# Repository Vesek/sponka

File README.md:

[English README](/README_en.md)
# sponka
RGB sponka na vlasy, postavená na flex PCB
### ***velice work in progress***
## Komponenty
- CH32V003
	- velice low-cost MCU, dostatečné na ovládání LED
	- chtěl jsem se s ním naučit
- WS2812B-MINI
	- Menší verze WS2812B
- TP4057
	- Nabíječ baterie s ochranou
	- můžete znát z většiny Li-ion nabíjecích desek z Aliexpressu
- DW01A
	- Ochrana samotné baterie
	- Některé baterie mají vestavěné, pro ostatní je zde
## Software
Software je napsaný s vývojovým prostředím [ch32v003fun](https://github.com/cnlohr/ch32v003fun) - open-source a lightweight stack pro programování těchto čipů

### Programování desky
Na desce jsou vyvedeny 3 piny pro SWIO. Výrobce čipu se bohužel rozhodl zavést
nestandardní "spin-off" SWD, takže potřebujete kompatibilní programátor.

Mimo oficiálního programátoru existují i SW programátory na různé MCU, některé lze najít v README [ch32v003fun](https://github.com/cnlohr/ch32v003fun),
existují ale i verze pro [Flipper Zero](https://github.com/sukvojte/wch_swio_flasher)a [RPi Pico](https://github.com/aappleby/picorvd).

Zapojení jednotlivých programátorů můžete najít v jejich README a
pinout SWIO je napsaný na spodní straně desky.

Software zkompilujete a nahrajete pomocí:
```bash
make
```
Nezapoměňte před tím stáhnout submoduly:
```bash
git submodule update --init
```

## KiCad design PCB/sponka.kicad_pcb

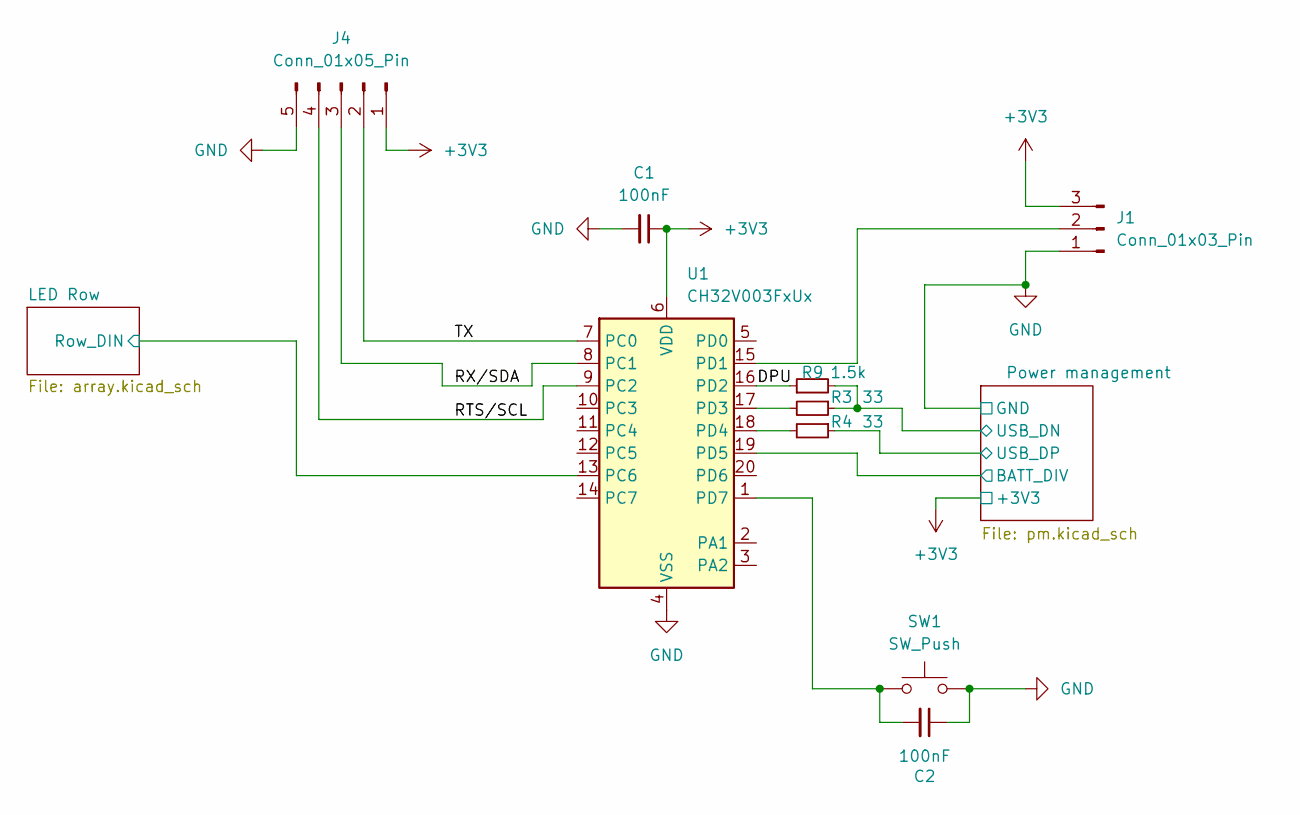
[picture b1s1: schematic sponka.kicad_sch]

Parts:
C1, C2: 100nF; C_0402_1005Metric
J1: Conn_01x03_Pin; pogo_pins_1_3
J4: Conn_01x05_Pin; pogo_pins_1_5
R3, R4: 33; R_0402_1005Metric
R9: 1.5k; R_0402_1005Metric
SW1: SW_Push; SW_SPST_B3U-1000P
U1: CH32V003FxUx; QFN-20-1EP_3x3mm_P0.4mm_EP1.65x1.65mm_ThermalVias

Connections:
+3V3: C1.1, J1.3, J4.1, U1.6 (VDD); also elsewhere on the board
/DPU: R9.1, U1.16 (PD2)
/LED Row/Row_DIN: U1.13 (PC6); also elsewhere on the board
/Power management/BATT_DIV: U1.19 (PD5); also elsewhere on the board
/Power management/USB_DN: R3.1, R9.2; also elsewhere on the board
/Power management/USB_DP: R4.1; also elsewhere on the board
/RTS/SCL: J4.4, U1.9 (PC2)
/RX/SDA: J4.3, U1.8 (PC1)
/TX: J4.2, U1.7 (PC0)
GND: C1.2, C2.1, J1.1, J4.5, SW1.2, U1.4 (VSS), U1.21 (VSS); also elsewhere on the board
unnamed: J1.2, U1.15 (PD1)
unnamed: R3.2, U1.17 (PD3)
unnamed: R4.2, U1.18 (PD4)
unnamed: C2.2, SW1.1, U1.1 (PD7)

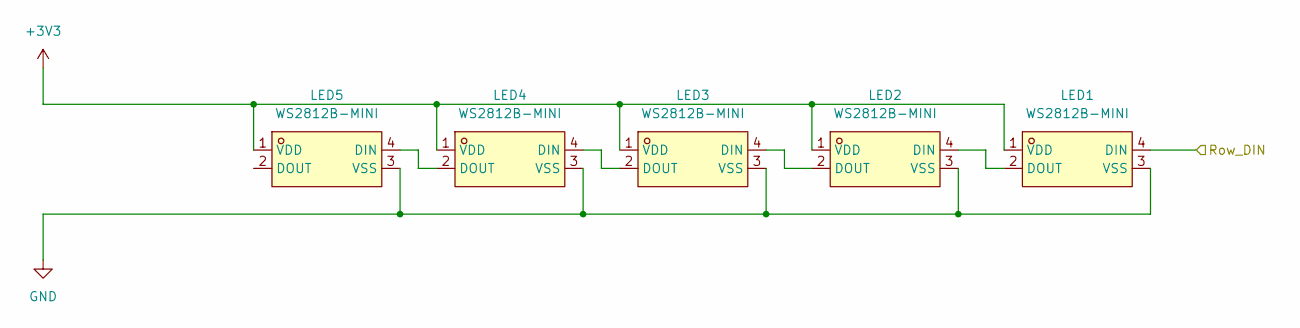
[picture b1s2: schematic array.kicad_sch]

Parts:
LED1, LED2, LED3, LED4, LED5: WS2812B-MINI; LED-SMD_4P-L3.5-W3.5-TL_WS2812B; LCSC Part C527089

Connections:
+3V3: LED1.1 (VDD), LED2.1 (VDD), LED3.1 (VDD), LED4.1 (VDD), LED5.1 (VDD); also elsewhere on the board
/LED Row/Row_DIN: LED1.4 (DIN); also elsewhere on the board
GND: LED1.3 (VSS), LED2.3 (VSS), LED3.3 (VSS), LED4.3 (VSS), LED5.3 (VSS); also elsewhere on the board
unnamed: LED1.2 (DOUT), LED2.4 (DIN)
unnamed: LED2.2 (DOUT), LED3.4 (DIN)
unnamed: LED3.2 (DOUT), LED4.4 (DIN)
unnamed: LED4.2 (DOUT), LED5.4 (DIN)

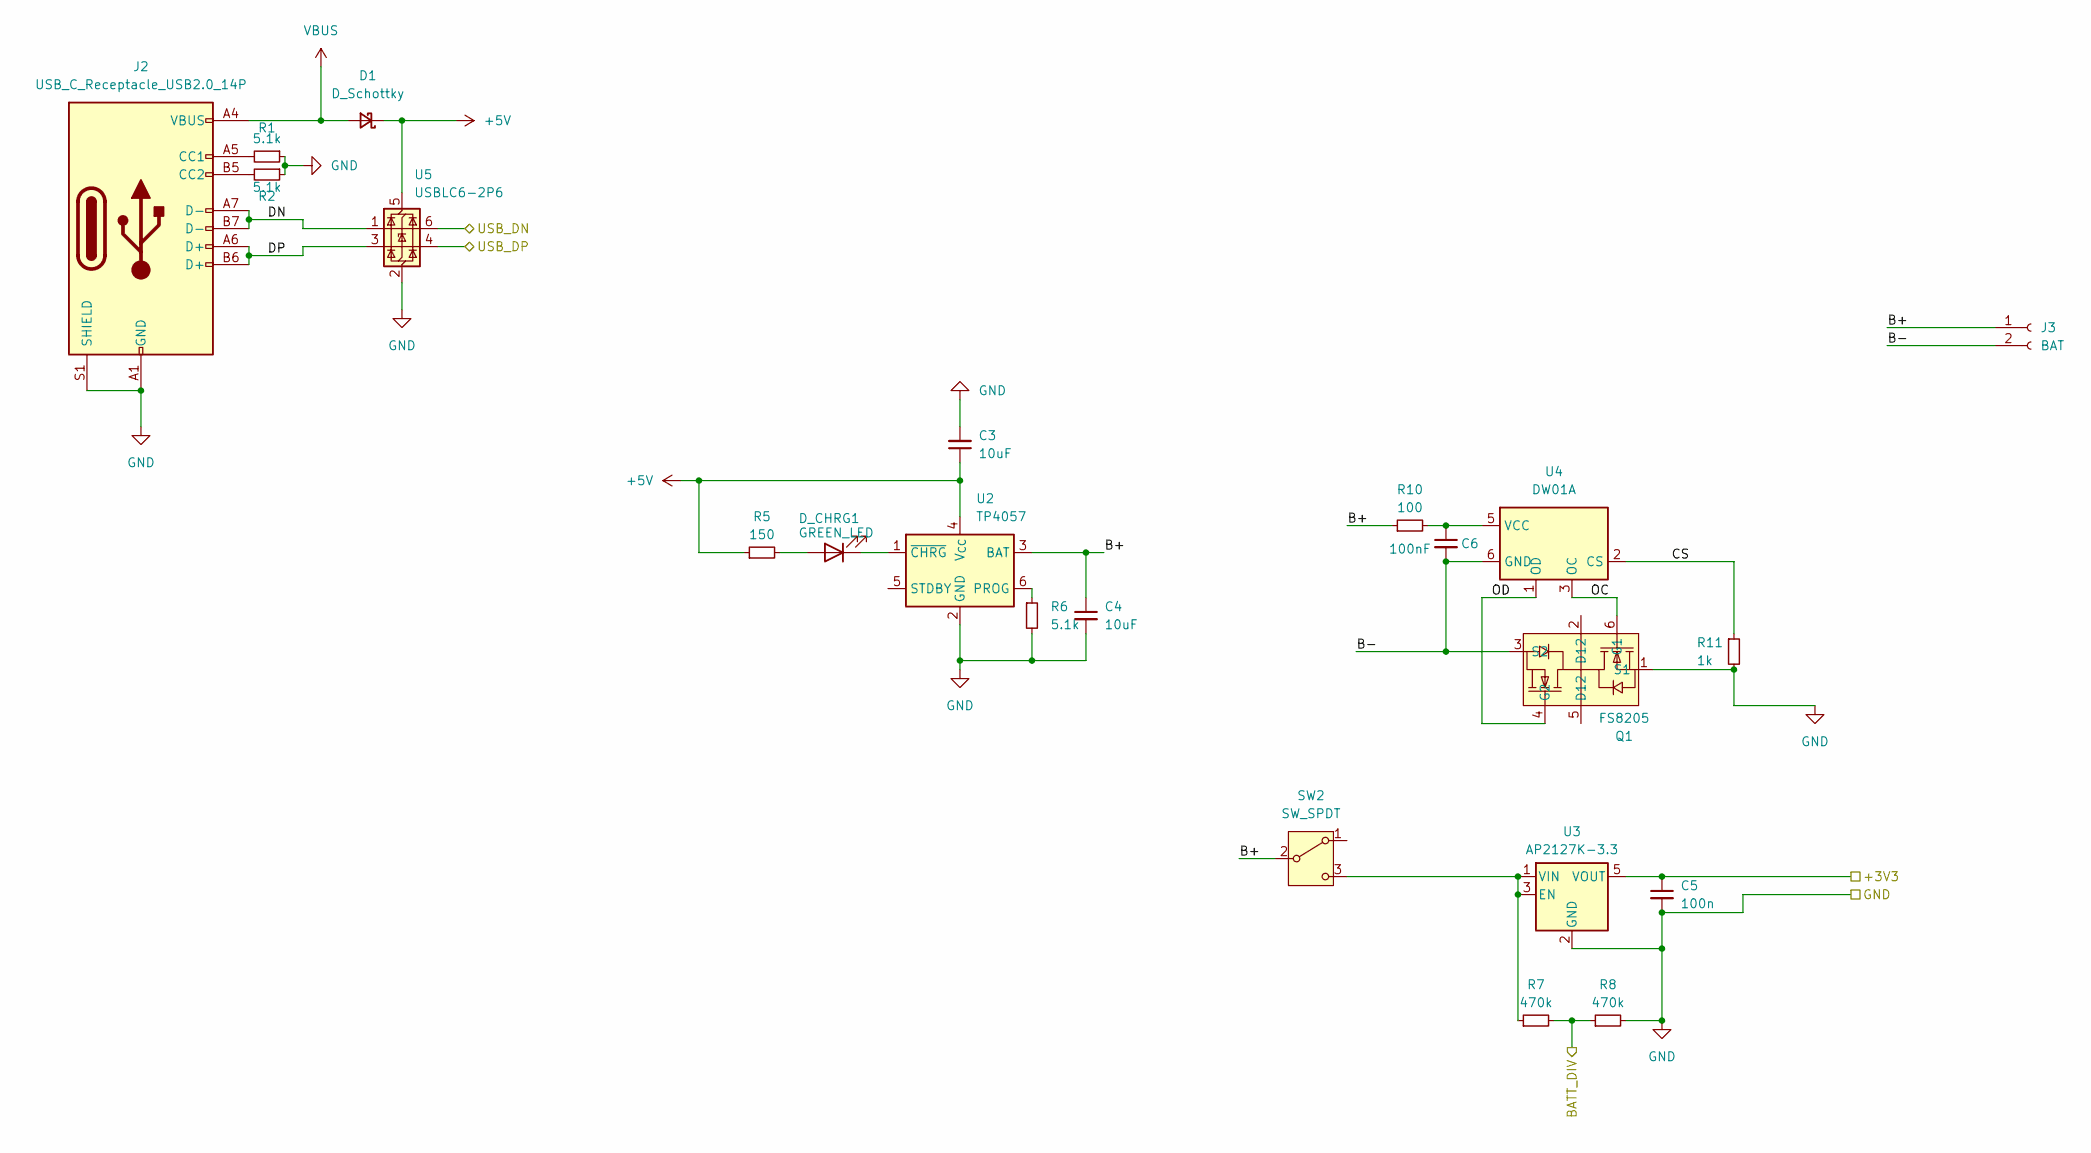
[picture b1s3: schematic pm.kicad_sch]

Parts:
C3, C4: 10uF; C_0402_1005Metric
C5: 100n; C_0402_1005Metric
C6: 100nF; C_0402_1005Metric
D1: D_Schottky; D_0402_1005Metric
D_CHRG1: GREEN_LED; LED_0603_1608Metric
J2: USB_C_Receptacle_USB2.0_14P; USB_C_Receptacle_G-Switch_GT-USB-7010ASV
J3: BAT; JST_SH_SM02B-SRSS-TB_1x02-1MP_P1.00mm_Horizontal
Q1: FS8205; SOT-23-6; LCSC Part C32254
R1, R2, R6: 5.1k; R_0402_1005Metric
R5: 150; R_0402_1005Metric
R7, R8: 470k; R_0402_1005Metric
R10: 100; R_0402_1005Metric
R11: 1k; R_0402_1005Metric
SW2: SW_SPDT; SW_SPDT_PCM12
U2: TP4057; TSOT-23-6
U3: AP2127K-3.3; SOT-23-5
U4: DW01A; SOT-23-6
U5: USBLC6-2P6; SOT-666

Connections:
+3V3: C5.1, U3.5 (VOUT); also elsewhere on the board
+5V: C3.1, D1.1 (K), R5.1, U2.4 (V_{CC}), U5.5 (VBUS)
/Power management/B+: C4.1, J3.1, R10.1, SW2.2 (B), U2.3 (BAT)
/Power management/B-: C6.2, J3.2, Q1.3 (S2), U4.6 (GND)
/Power management/BATT_DIV: R7.2, R8.1; also elsewhere on the board
/Power management/CS: R11.1, U4.2 (CS)
/Power management/DN: J2.A7 (D-), J2.B7 (D-), U5.1 (I/O1)
/Power management/DP: J2.A6 (D+), J2.B6 (D+), U5.3 (I/O2)
/Power management/OC: Q1.6 (G1), U4.3 (OC)
/Power management/OD: Q1.4 (G2), U4.1 (OD)
/Power management/USB_DN: U5.6 (I/O1); also elsewhere on the board
/Power management/USB_DP: U5.4 (I/O2); also elsewhere on the board
GND: C3.2, C4.2, C5.2, J2.A1 (GND), J2.A12 (GND), J2.B1 (GND), J2.B12 (GND), J2.S1 (SHIELD), Q1.1 (S1), R1.1, R2.1, R6.2, R8.2, R11.2, U2.2 (GND), U3.2 (GND), U5.2 (GND); also elsewhere on the board
unnamed: D_CHRG1.2 (A), R5.2
unnamed: D_CHRG1.1 (K), U2.1 (~CHRG)
unnamed: J2.A5 (CC1), R1.2
unnamed: J2.B5 (CC2), R2.2
unnamed: R7.1, SW2.3 (C), U3.1 (VIN), U3.3 (EN)
unnamed: R6.1, U2.6 (PROG)
unnamed: C6.1, R10.2, U4.5 (VCC)
VBUS: D1.2 (A), J2.A4 (VBUS), J2.A9 (VBUS), J2.B4 (VBUS), J2.B9 (VBUS)

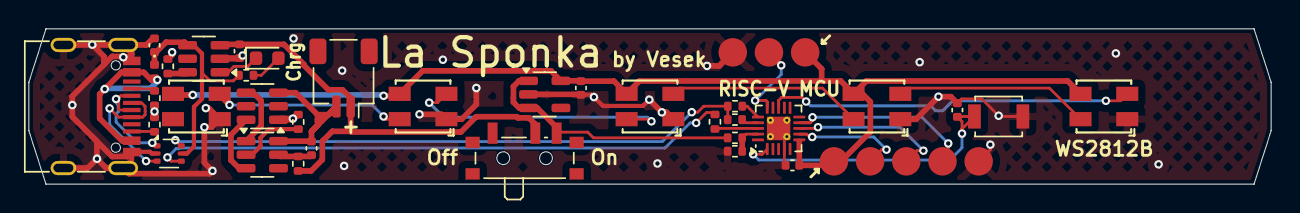
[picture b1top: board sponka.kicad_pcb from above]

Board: 2 copper layers, 87.2 x 10.9 mm, 36 parts (0 on the bottom side), 34 nets.

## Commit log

2024-09-05 Made first PCB
2024-09-06 PCB V2
2024-09-07 New PCB design
2024-09-07 New PCB revision
2024-09-08 Probably the final update
2024-09-08 Small updates to PCB
2024-09-10 Made smol :) Anyway, this is just WIP, still working on it
2024-09-10 Progress update
2024-09-11 Probably done?
2024-09-12 Add battery connector 3D models
2024-09-12 New design WIP
2024-09-12 Ma favorite design yet!
2024-09-12 Update silkscreen
2024-09-13 Update the backside
2024-09-14 Change the battery connector resolve issues
2024-09-18 Add battery protection circuit
2024-09-18 Add protection circuit to PCB I don't like the design tho, so let's fix that
2024-12-20 Add USBLC6-2P6 for ESD protection The usual COMPLETE REDESIGN because it didn't fit
2024-12-20 Replace 5k with 5.1k resistor Resistor for limiting charging current, it is within tolerance - eliminating one SKU
2024-12-20 Small polishing touches Move vias out of the way of silkscreen and vice versa
2024-12-24 Change LED resistor value
2024-12-28 Update PCB
2024-12-28 Change LED and it's resistor Once again, i found i had this laying around
2025-01-26 Fix wrong values
2025-01-27 Add WIP software
2025-01-27 Update README Add an english README
2025-01-27 Fix english README link
